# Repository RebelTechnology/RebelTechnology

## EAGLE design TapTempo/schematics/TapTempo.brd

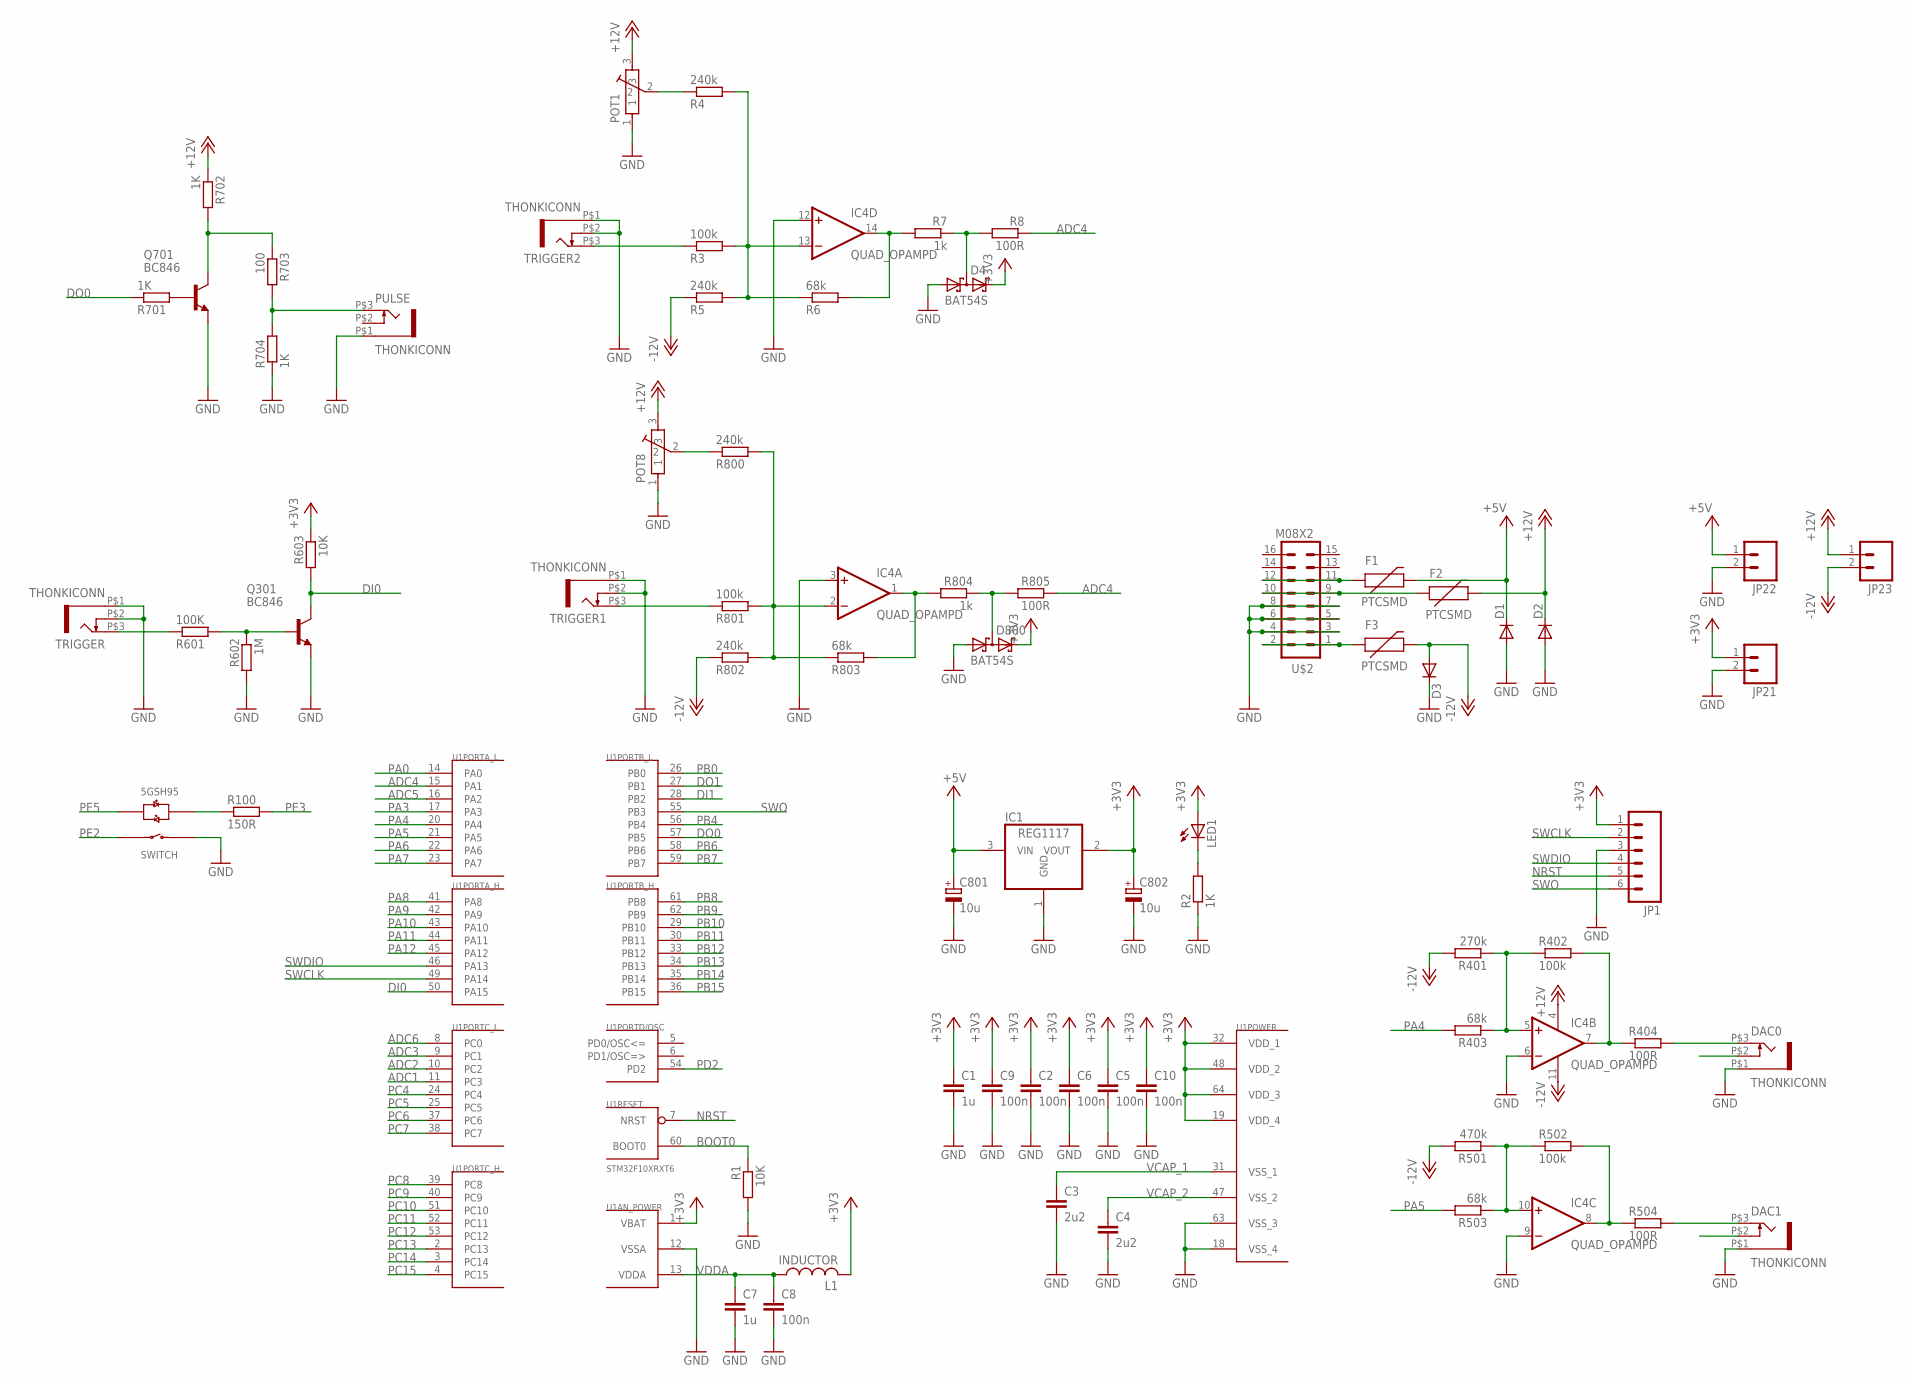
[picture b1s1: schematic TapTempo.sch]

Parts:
C1, C7: 1u; C0603
C2, C5, C6, C8, C9, C10: 100n; C0603
C3, C4: 2u2; C0603
C801, C802: 10u; PANASONIC_A
D1, D2, D3: DIODESMA; SMA-DIODE
D4, D800: BAT54S; SOT23
DAC0, DAC1: THONKICONN
F1, F2, F3: PTCSMD; PTC-1206
IC1: REG1117; SOT223
IC4: QUAD_OPAMPD; SO14
JP1: M06SIP; 1X06
JP21, JP22, JP23: M02PTH; 1X02
L1: INDUCTOR; 0603@1
LED1: LEDCHIPLED_0603; CHIPLED_0603
POT1, POT8: POT-ALPS-RK09L1140
PULSE: THONKICONN
Q301, Q701: BC846; SOT23
R1, R603: 10K; R0603
R2, R701, R702, R704: 1K; R0603
R3, R801: 100k; 0603
R4, R5, R800, R802: 240k; 0603
R6, R803: 68k; 0603
R7, R804: 1k; 0603
R8, R805: 100R; 0603
R100: 150R; 0603
R401: 270k; R0603
R402, R502: 100k; R0603
R403, R503: 68k; R0603
R404, R504: 100R; R0603
R501: 470k; R0603
R601: 100K; R0603
R602: 1M; R0603
R703: 100; R0603
TRIGGER, TRIGGER1, TRIGGER2: THONKICONN
U1: STM32F10XRXT6; TQFP64
U$1: 5GTH9
U$2: M08X2; 2X8

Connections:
+3V3: C1.1, C2.1, C5.1, C6.1, C9.1, C10.1, C802.+, D4.2 (C2), D800.2 (C2), IC1.2 (VOUT), JP1.1, JP21.1, L1.2, LED1.A, R603.1, U1.1 (VBAT), U1.19 (VDD_4), U1.32 (VDD_1), U1.48 (VDD_2), U1.64 (VDD_3)
+5V: C801.+, D1.C, F1.2, IC1.3 (VIN), JP22.1
+12V: D2.C, F2.2, IC4.4 (V+), JP23.1, POT1.3, POT8.3, R702.1
-12V: D3.A, F3.2, IC4.11 (V-), JP23.2, R5.1, R401.2, R501.2, R802.1
ADC1: U1.11 (PC3)
ADC2: U1.10 (PC2)
ADC3: U1.9 (PC1)
ADC4: R8.1, R805.1, U1.15 (PA1)
ADC5: U1.16 (PA2)
ADC6: U1.8 (PC0)
BOOT0: R1.1, U1.60 (BOOT0)
DI0: Q301.3 (C), R603.2, U1.50 (PA15)
DI1: U1.28 (PB2)
DO0: R701.1, U1.57 (PB5)
DO1: U1.27 (PB1)
GND: C1.2, C2.2, C3.2, C4.2, C5.2, C6.2, C7.2, C8.2, C9.2, C10.2, C801.-, C802.-, D1.A, D2.A, D3.C, D4.1 (A1), D800.1 (A1), DAC0.P$1 (5), DAC1.P$1 (5), IC1.1 (GND), IC4.3 (+IN), IC4.6 (-IN), IC4.9 (-IN), IC4.12 (+IN), JP1.3, JP21.2, JP22.2, POT1.1, POT8.1, PULSE.P$1 (5), Q301.2 (E), Q701.2 (E), R1.2, R2.1, R602.2, R704.1, TRIGGER.P$1 (5), TRIGGER.P$2 (4), TRIGGER1.P$1 (5), TRIGGER1.P$2 (4), TRIGGER2.P$1 (5), TRIGGER2.P$2 (4), U1.12 (VSSA), U1.18 (VSS_4), U1.63 (VSS_3), U$1.1 (SWITCH_B), U$2.3, U$2.4, U$2.5, U$2.6, U$2.7, U$2.8
unnamed: R801.1, TRIGGER1.P$3 (3)
unnamed: POT8.2, R800.1
unnamed: IC4.1 (OUT), R803.2, R804.2
unnamed: R3.1, TRIGGER2.P$3 (3)
unnamed: IC4.8 (OUT), R502.2, R504.1
unnamed: F3.1, U$2.1, U$2.2
unnamed: IC4.7 (OUT), R402.2, R404.1
unnamed: IC4.13 (-IN), R3.2, R4.2, R5.2, R6.1
unnamed: R100.1, U$1.+3 (LED_R+)
unnamed: POT1.2, R4.1
unnamed: IC4.14 (OUT), R6.2, R7.2
unnamed: IC4.5 (+IN), R401.1, R402.1, R403.1
unnamed: D4.3 (C1A2), R7.1, R8.2
unnamed: IC4.10 (+IN), R501.1, R502.1, R503.1
unnamed: LED1.C, R2.2
unnamed: R601.1, TRIGGER.P$3 (3)
unnamed: Q301.1 (B), R601.2, R602.1
unnamed: DAC0.P$3 (3), R404.2
unnamed: DAC1.P$3 (3), R504.2
unnamed: IC4.2 (-IN), R800.2, R801.2, R802.2, R803.1
unnamed: Q701.1 (B), R701.2
unnamed: PULSE.P$3 (3), R703.2, R704.2
unnamed: D800.3 (C1A2), R804.1, R805.2
unnamed: Q701.3 (C), R702.2, R703.1
unnamed: F1.1, U$2.11, U$2.12
unnamed: F2.1, U$2.9, U$2.10
NRST: JP1.5, U1.7 (NRST)
PA0: U1.14 (PA0)
PA3: U1.17 (PA3)
PA4: R403.2, U1.20 (PA4)
PA5: R503.2, U1.21 (PA5)
PA6: U1.22 (PA6)
PA7: U1.23 (PA7)
PA8: U1.41 (PA8)
PA9: U1.42 (PA9)
PA10: U1.43 (PA10)
PA11: U1.44 (PA11)
PA12: U1.45 (PA12)
PB0: U1.26 (PB0)
PB4: U1.56 (PB4)
PB6: U1.58 (PB6)
PB7: U1.59 (PB7)
PB8: U1.61 (PB8)
PB9: U1.62 (PB9)
PB10: U1.29 (PB10)
PB11: U1.30 (PB11)
PB12: U1.33 (PB12)
PB13: U1.34 (PB13)
PB14: U1.35 (PB14)
PB15: U1.36 (PB15)
PC4: U1.24 (PC4)
PC5: U1.25 (PC5)
PC6: U1.37 (PC6)
PC7: U1.38 (PC7)
PC8: U1.39 (PC8)
PC9: U1.40 (PC9)
PC10: U1.51 (PC10)
PC11: U1.52 (PC11)
PC12: U1.53 (PC12)
PC13: U1.2 (PC13)
PC14: U1.3 (PC14)
PC15: U1.4 (PC15)
PD2: U1.54 (PD2)
PE2: U$1.4 (SWITCH_A)
PE3: R100.2
PE5: U$1.-2 (LED_G+)
SWCLK: JP1.2, U1.49 (PA14)
SWDIO: JP1.4, U1.46 (PA13)
SWO: JP1.6, U1.55 (PB3)
VCAP_1: C3.1, U1.31 (VSS_1)
VCAP_2: C4.1, U1.47 (VSS_2)
VDDA: C7.1, C8.1, L1.1, U1.13 (VDDA)

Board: 2 copper layers, 72 parts (0 on the bottom side), 44 nets, no tracks yet.

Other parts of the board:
U$3: RT-LOGO-35MM-BL

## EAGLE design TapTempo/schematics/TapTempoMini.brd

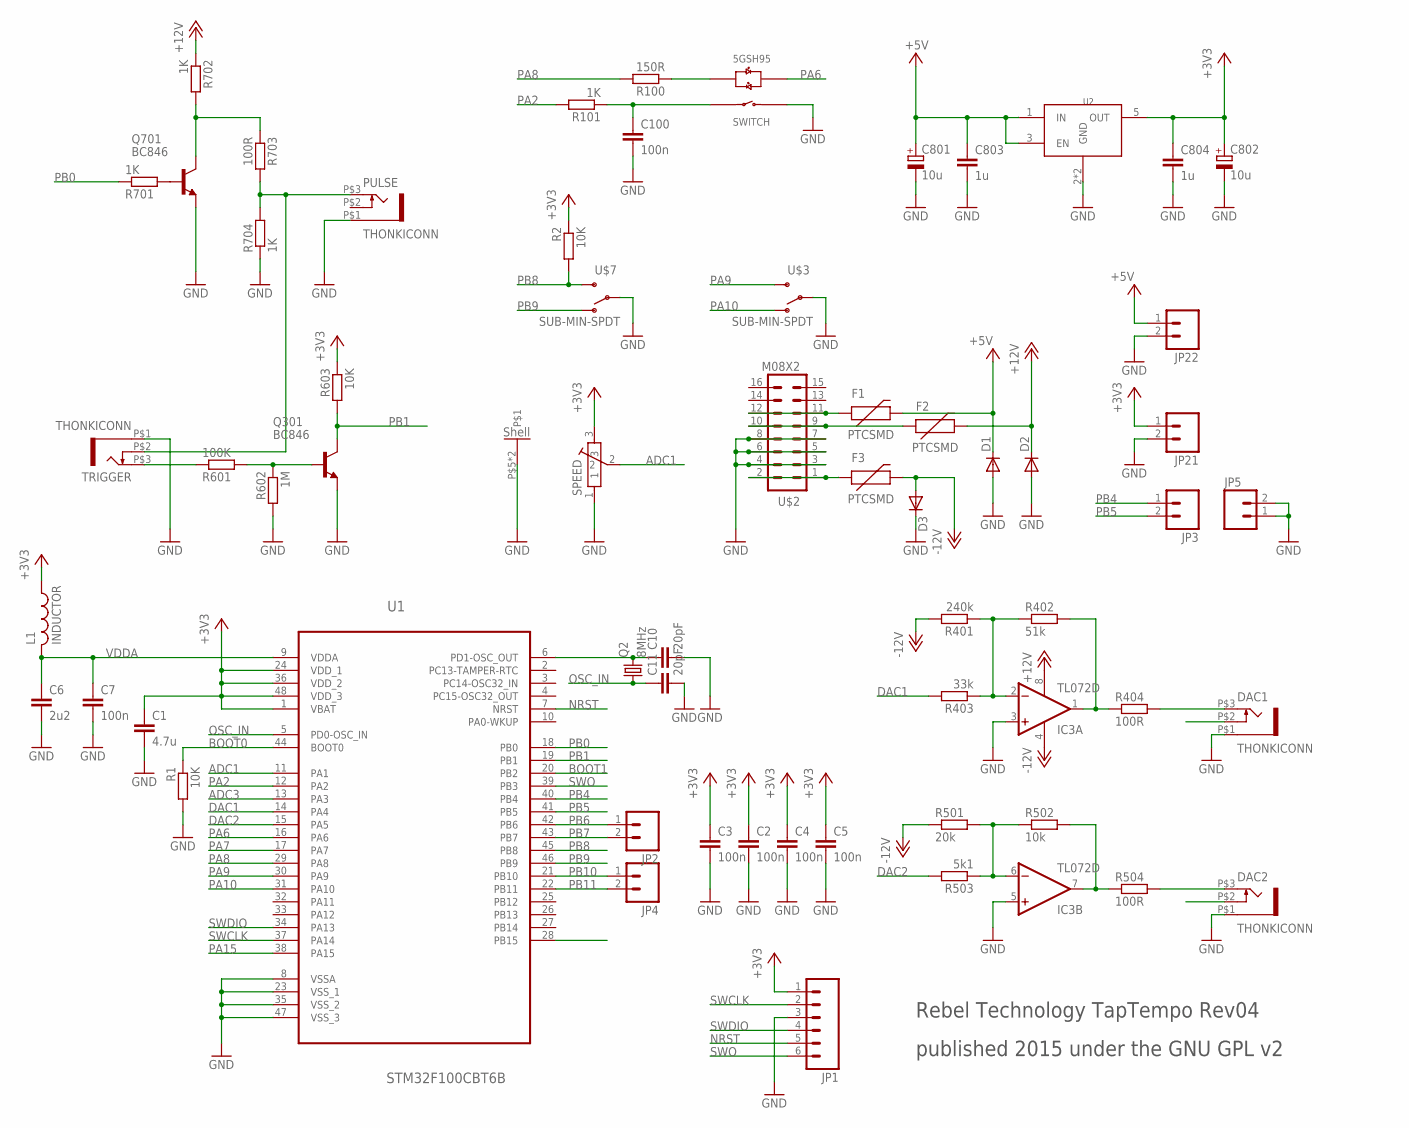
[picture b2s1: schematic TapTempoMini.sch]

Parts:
C1: 4.7u; C0603
C2, C3, C4, C5, C7, C100: 100n; C0603
C6: 2u2; C0603
C10, C11: 20pF; C0603
C801, C802: 10u; SANYO-OSCON_SMD_A5
C803, C804: 1u; C0603
D1, D2, D3: DIODESMA; SMA-DIODE
DAC1, DAC2: THONKICONN
F1, F2, F3: PTCSMD; PTC-1206
IC3: TL072D; SO08
JP1: M06SIP; 1X06
JP2, JP3, JP4, JP5, JP21, JP22: M02PTH; 1X02
L1: INDUCTOR; 0603
PULSE: THONKICONN
Q2: 8MHz; HC49UP; FARNELL 206-3972
Q301, Q701: BC846; SOT23
R1, R2, R603: 10K; R0603
R100: 150R; 0603
R101, R701, R702, R704: 1K; R0603
R401: 240k; R0603
R402: 51k; R0603
R403: 33k; R0603
R404, R504, R703: 100R; R0603
R501: 20k; R0603
R502: 10k; R0603
R503: 5k1; R0603
R601: 100K; R0603
R602: 1M; R0603
SPEED: POT-ALPS-RK09L1140
TRIGGER: THONKICONN
U1: STM32F100CBT6B; QFP50P900X900X160-48N
U2: NCP702; TSOP-5
U$1: 5GTH9
U$2: M08X2; 2X8
U$3, U$7: SUB-MIN-SPDT

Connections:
+3V3: C1.1, C2.1, C3.1, C4.1, C5.1, C802.+, C804.1, JP1.1, JP21.1, L1.1, R2.1, R603.1, SPEED.3, U1.1 (VBAT), U1.24 (VDD_1), U1.36 (VDD_2), U1.48 (VDD_3), U2.5 (OUT)
+5V: C801.+, C803.1, D1.C, F1.2, JP22.1, U2.1 (IN), U2.3 (EN)
+12V: D2.C, F2.2, IC3.8 (V+), R702.1
-12V: D3.A, F3.2, IC3.4 (V-), R401.2, R501.1
ADC1: SPEED.2, U1.11 (PA1)
ADC3: U1.13 (PA3)
BOOT0: R1.1, U1.44 (BOOT0)
BOOT1: U1.20 (PB2)
DAC1: R403.2, U1.14 (PA4)
DAC2: R503.2, U1.15 (PA5)
GND: C1.2, C2.2, C3.2, C4.2, C5.2, C6.2, C7.2, C10.2, C11.2, C100.2, C801.-, C802.-, C803.2, C804.2, D1.A, D2.A, D3.C, DAC1.P$1 (5), DAC2.P$1 (5), IC3.3 (+IN), IC3.5 (+IN), JP1.3, JP5.1, JP5.2, JP21.2, JP22.2, PULSE.P$1 (5), Q301.2 (E), Q701.2 (E), R1.2, R602.2, R704.1, SPEED.1, SPEED.P$5, SPEED.P$6, TRIGGER.P$1 (5), U1.8 (VSSA), U1.23 (VSS_1), U1.35 (VSS_2), U1.47 (VSS_3), U2.2 (GND), U2.4 (GND), U$1.1 (SWITCH_B), U$2.3, U$2.4, U$2.5, U$2.6, U$2.7, U$2.8, U$3.2, U$7.2
unnamed: C10.1, Q2.2, U1.6 (PD1-OSC_OUT)
unnamed: R100.1, U$1.-2 (LED_G+)
unnamed: IC3.7 (OUT), R502.2, R504.1
unnamed: IC3.6 (-IN), R501.2, R502.1, R503.1
unnamed: PULSE.P$3 (3), R703.2, R704.2, TRIGGER.P$2 (4)
unnamed: F3.1, U$2.1, U$2.2
unnamed: IC3.1 (OUT), R402.2, R404.1
unnamed: IC3.2 (-IN), R401.1, R402.1, R403.1
unnamed: R601.1, TRIGGER.P$3 (3)
unnamed: Q301.1 (B), R601.2, R602.1
unnamed: DAC1.P$3 (3), R404.2
unnamed: DAC2.P$3 (3), R504.2
unnamed: Q701.1 (B), R701.2
unnamed: Q701.3 (C), R702.2, R703.1
unnamed: F1.1, U$2.11, U$2.12
unnamed: F2.1, U$2.9, U$2.10
NRST: JP1.5, U1.7 (NRST)
OSC_IN: C11.1, Q2.1, U1.5 (PD0-OSC_IN)
PA2: R101.2, U1.12 (PA2)
PA6: U1.16 (PA6), U$1.+3 (LED_R+)
PA7: U1.17 (PA7)
PA8: R100.2, U1.29 (PA8)
PA9: U1.30 (PA9), U$3.3 (S)
PA10: U1.31 (PA10), U$3.1 (O)
PA15: U1.38 (PA15)
PB0: R701.1, U1.18 (PB0)
PB1: Q301.3 (C), R603.2, U1.19 (PB1)
PB4: JP3.1, U1.40 (PB4)
PB5: JP3.2, U1.41 (PB5)
PB6: JP2.1, U1.42 (PB6)
PB7: JP2.2, U1.43 (PB7)
PB8: R2.2, U1.45 (PB8), U$7.3 (S)
PB9: U1.46 (PB9), U$7.1 (O)
PB10: JP4.1, U1.21 (PB10)
PB11: JP4.2, U1.22 (PB11)
SWCLK: JP1.2, U1.37 (PA14)
SWDIO: JP1.4, U1.34 (PA13)
SWITCH_A: C100.1, R101.1, U$1.4 (SWITCH_A)
SWO: JP1.6, U1.39 (PB3)
VDDA: C6.1, C7.1, L1.2, U1.9 (VDDA)

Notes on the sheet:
Rebel Technology TapTempo Rev04
published 2015 under the GNU GPL v2

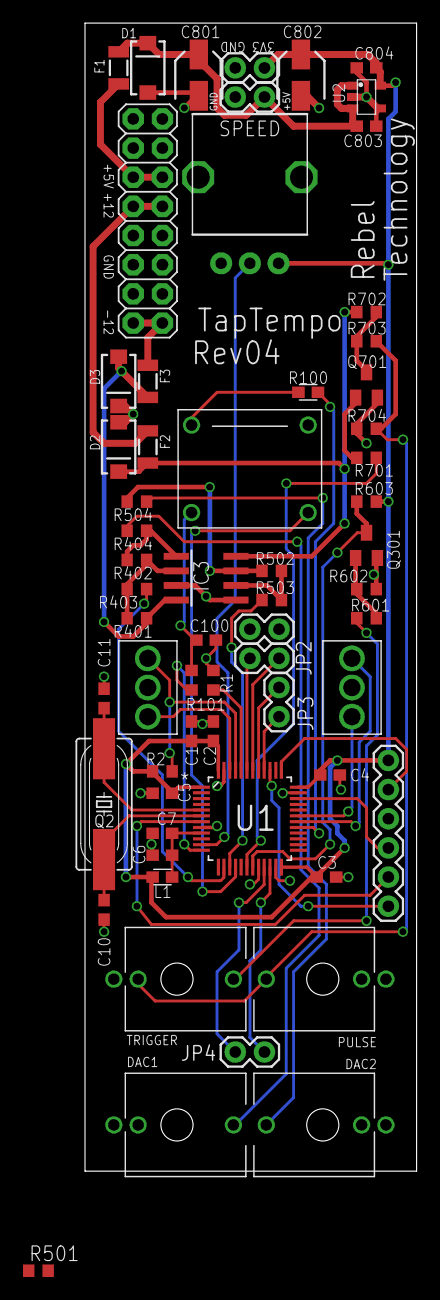
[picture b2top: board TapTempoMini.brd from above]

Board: 2 copper layers, 28.9 x 100.0 mm, 62 parts (0 on the bottom side), 47 nets.

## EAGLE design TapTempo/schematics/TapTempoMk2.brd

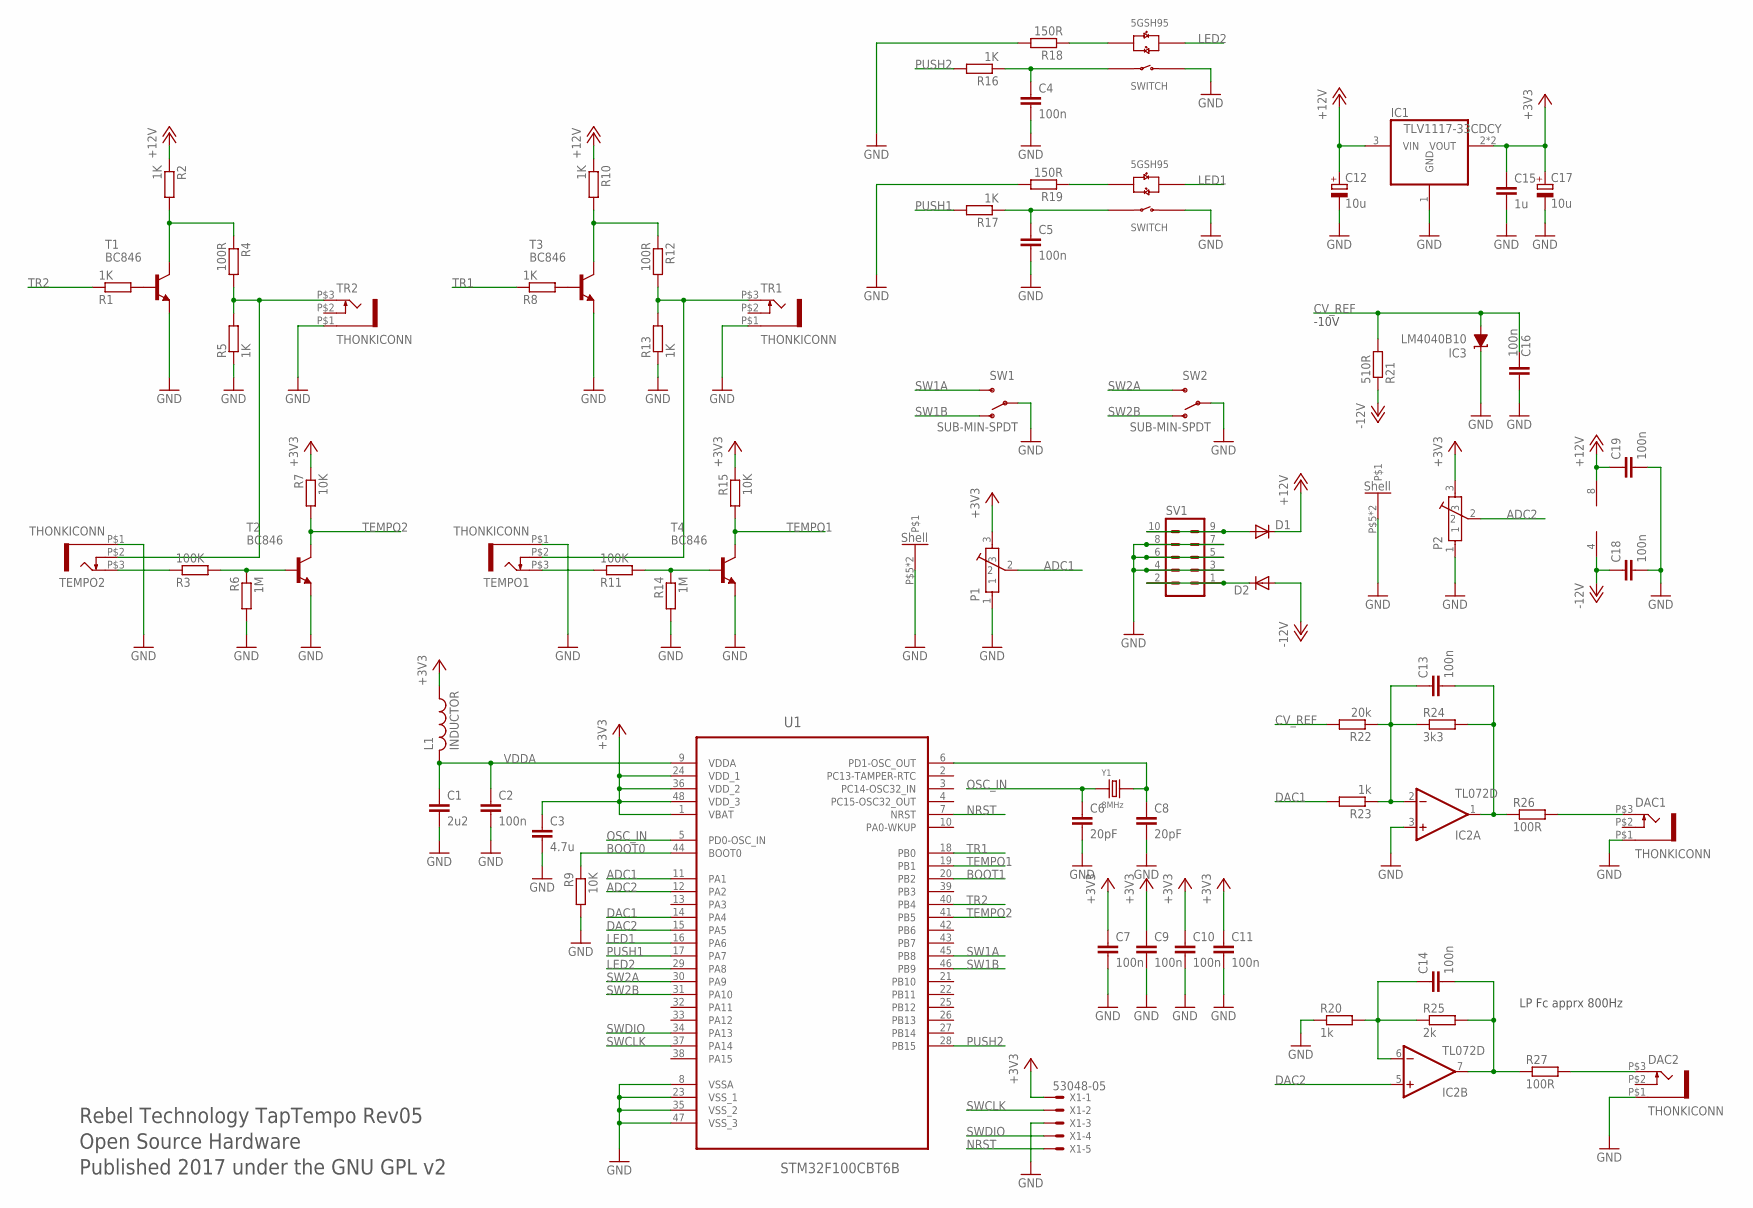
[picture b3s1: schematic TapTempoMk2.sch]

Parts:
C1: 2u2; C0603
C2, C4, C5, C7, C9, C10, C11, C13, C14, C16, C18, C19: 100n; C0603
C3: 4.7u; C0603
C6, C8: 20pF; C0603
C12, C17: 10u; PANASONIC_A; FARNELL 882-3014
C15: 1u; C0603
D1, D2: DIODESMA; SMA-DIODE
DAC1, DAC2: THONKICONN
IC1: TLV1117-33CDCY; SOT223; FARNELL 149-4942
IC2: TL072D; SO08
IC3: LM4040B10; DBZ_R-PDSO-G3
L1: INDUCTOR; 0603
P1, P2: POT-ALPS-RK09L1140
PUSH1, PUSH2: 5GTH9
R1, R2, R5, R8, R10, R13, R16, R17: 1K; 0603
R3, R11: 100K; 0603
R4, R12, R26, R27: 100R; 0603
R6, R14: 1M; 0603
R7, R9, R15: 10K; 0603
R18, R19: 150R; 0603
R20, R23: 1k; 0603
R21: 510R; 0603
R22: 20k; 0603
R24: 3k3; 0603
R25: 2k; 0603
SV1: MA05-2
SW1, SW2: SUB-MIN-SPDT
T1, T2, T3, T4: BC846; SOT23
TEMPO1, TEMPO2: THONKICONN
TR1, TR2: THONKICONN
U1: STM32F100CBT6B; QFP50P900X900X160-48N
X1: 53048-05
Y1: 8MHz; X2-SMD-5.0X3.2X1.3MM

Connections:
+3V3: C3.1, C7.1, C9.1, C10.1, C11.1, C15.1, C17.+, IC1.2 (VOUT), IC1.4 (VOUT), L1.1, P1.3, P2.3, R7.1, R15.1, U1.1 (VBAT), U1.24 (VDD_1), U1.36 (VDD_2), U1.48 (VDD_3), X1.1
+12V: C12.+, C19.1, D1.C, IC1.3 (VIN), IC2.8 (V+), R2.1, R10.1
-12V: C18.1, D2.A, IC2.4 (V-), R21.1
ADC1: P1.2, U1.11 (PA1)
ADC2: P2.2, U1.12 (PA2)
BOOT0: R9.1, U1.44 (BOOT0)
BOOT1: U1.20 (PB2)
CV_REF: C16.1, IC3.2 (A), R21.2, R22.2
DAC1: R23.2, U1.14 (PA4)
DAC2: IC2.5 (+IN), U1.15 (PA5)
GND: C1.2, C2.2, C3.2, C4.2, C5.2, C6.2, C7.2, C8.2, C9.2, C10.2, C11.2, C12.-, C15.2, C16.2, C17.-, C18.2, C19.2, DAC1.P$1 (5), DAC2.P$1 (5), IC1.1 (GND), IC2.3 (+IN), IC3.1 (C), P1.1, P1.P$5, P1.P$6, P2.1, P2.P$5, P2.P$6, PUSH1.1 (SWITCH_B), PUSH2.1 (SWITCH_B), R5.1, R6.2, R9.2, R13.1, R14.2, R18.2, R19.2, R20.1, SV1.3, SV1.4, SV1.5, SV1.6, SV1.7, SV1.8, SW1.2, SW2.2, T1.2 (E), T2.2 (E), T3.2 (E), T4.2 (E), TEMPO1.P$1 (5), TEMPO2.P$1 (5), TR1.P$1 (5), TR2.P$1 (5), U1.8 (VSSA), U1.23 (VSS_1), U1.35 (VSS_2), U1.47 (VSS_3), X1.3
LED1: PUSH1.+3 (LED_R+), U1.16 (PA6)
LED2: PUSH2.+3 (LED_R+), U1.29 (PA8)
unnamed: C8.1, U1.6 (PD1-OSC_OUT), Y1.2
unnamed: PUSH1.-2 (LED_G+), R19.1
unnamed: C14.2, IC2.7 (OUT), R25.2, R27.1
unnamed: C14.1, IC2.6 (-IN), R20.2, R25.1
unnamed: R12.2, R13.2, TEMPO1.P$2 (4), TR1.P$3 (3)
unnamed: D1.A, SV1.9, SV1.10
unnamed: C13.2, IC2.1 (OUT), R24.2, R26.1
unnamed: PUSH2.-2 (LED_G+), R18.1
unnamed: R3.2, R6.1, T2.1 (B)
unnamed: R1.2, T1.1 (B)
unnamed: R2.2, R4.1, T1.3 (C)
unnamed: C13.1, IC2.2 (-IN), R22.1, R23.1, R24.1
unnamed: R3.1, TEMPO2.P$3 (3)
unnamed: R4.2, R5.2, TEMPO2.P$2 (4), TR2.P$3 (3)
unnamed: D2.C, SV1.1, SV1.2
unnamed: C5.1, PUSH1.4 (SWITCH_A), R17.1
unnamed: C4.1, PUSH2.4 (SWITCH_A), R16.1
unnamed: R11.1, TEMPO1.P$3 (3)
unnamed: R11.2, R14.1, T4.1 (B)
unnamed: DAC1.P$3 (3), R26.2
unnamed: DAC2.P$3 (3), R27.2
unnamed: R8.2, T3.1 (B)
unnamed: R10.2, R12.1, T3.3 (C)
NRST: U1.7 (NRST), X1.5
OSC_IN: C6.1, U1.5 (PD0-OSC_IN), Y1.1
PUSH1: R17.2, U1.17 (PA7)
PUSH2: R16.2, U1.28 (PB15)
SW1A: SW1.3 (S), U1.45 (PB8)
SW1B: SW1.1 (O), U1.46 (PB9)
SW2A: SW2.3 (S), U1.30 (PA9)
SW2B: SW2.1 (O), U1.31 (PA10)
SWCLK: U1.37 (PA14), X1.2
SWDIO: U1.34 (PA13), X1.4
TEMPO1: R15.2, T4.3 (C), U1.19 (PB1)
TEMPO2: R7.2, T2.3 (C), U1.41 (PB5)
TR1: R8.1, U1.18 (PB0)
TR2: R1.1, U1.40 (PB4)
VDDA: C1.1, C2.1, L1.2, U1.9 (VDDA)

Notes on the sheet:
Rebel Technology TapTempo Rev05
Published 2017 under the GNU GPL v2
LP Fc apprx 800Hz
-10V
Open Source Hardware

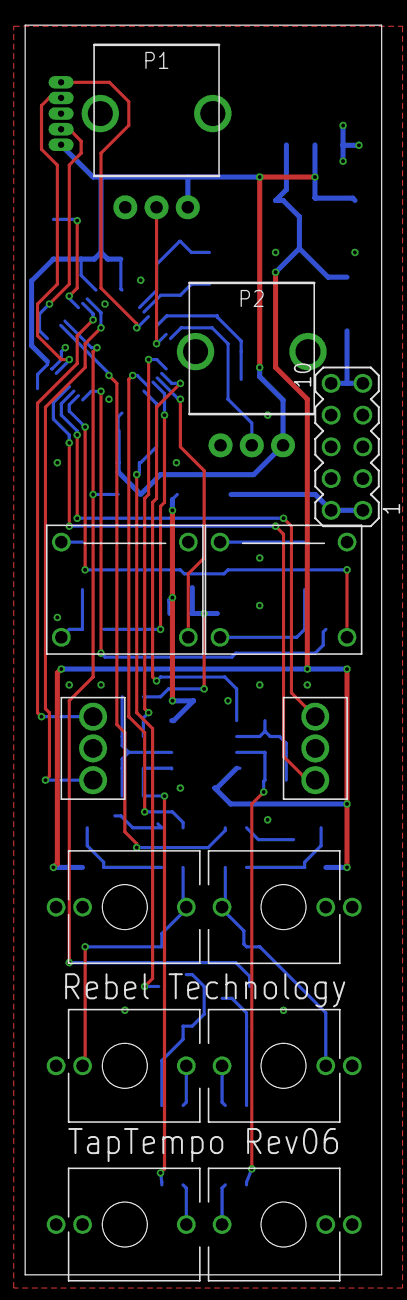
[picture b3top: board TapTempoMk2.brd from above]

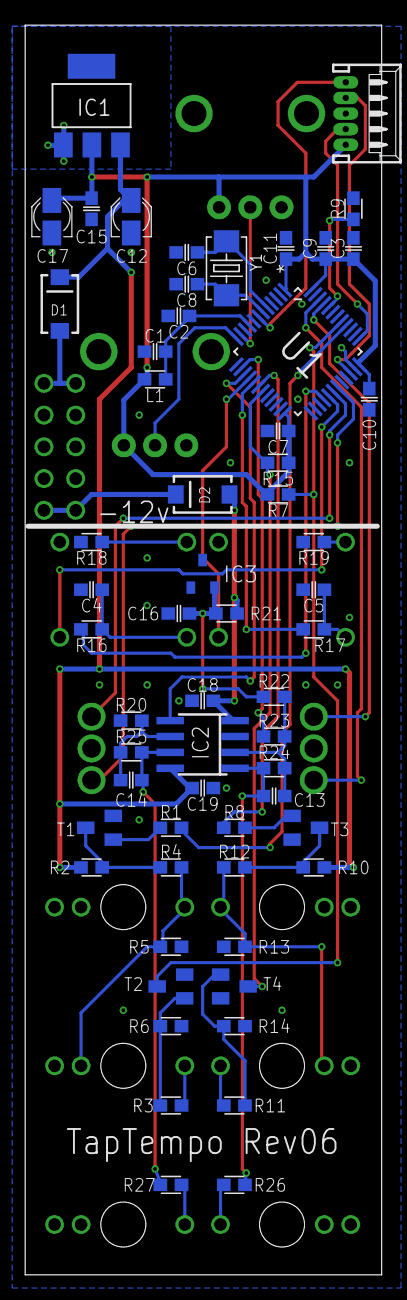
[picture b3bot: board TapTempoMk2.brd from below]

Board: 2 copper layers, 28.5 x 100.0 mm, 72 parts (59 on the bottom side), 50 nets.

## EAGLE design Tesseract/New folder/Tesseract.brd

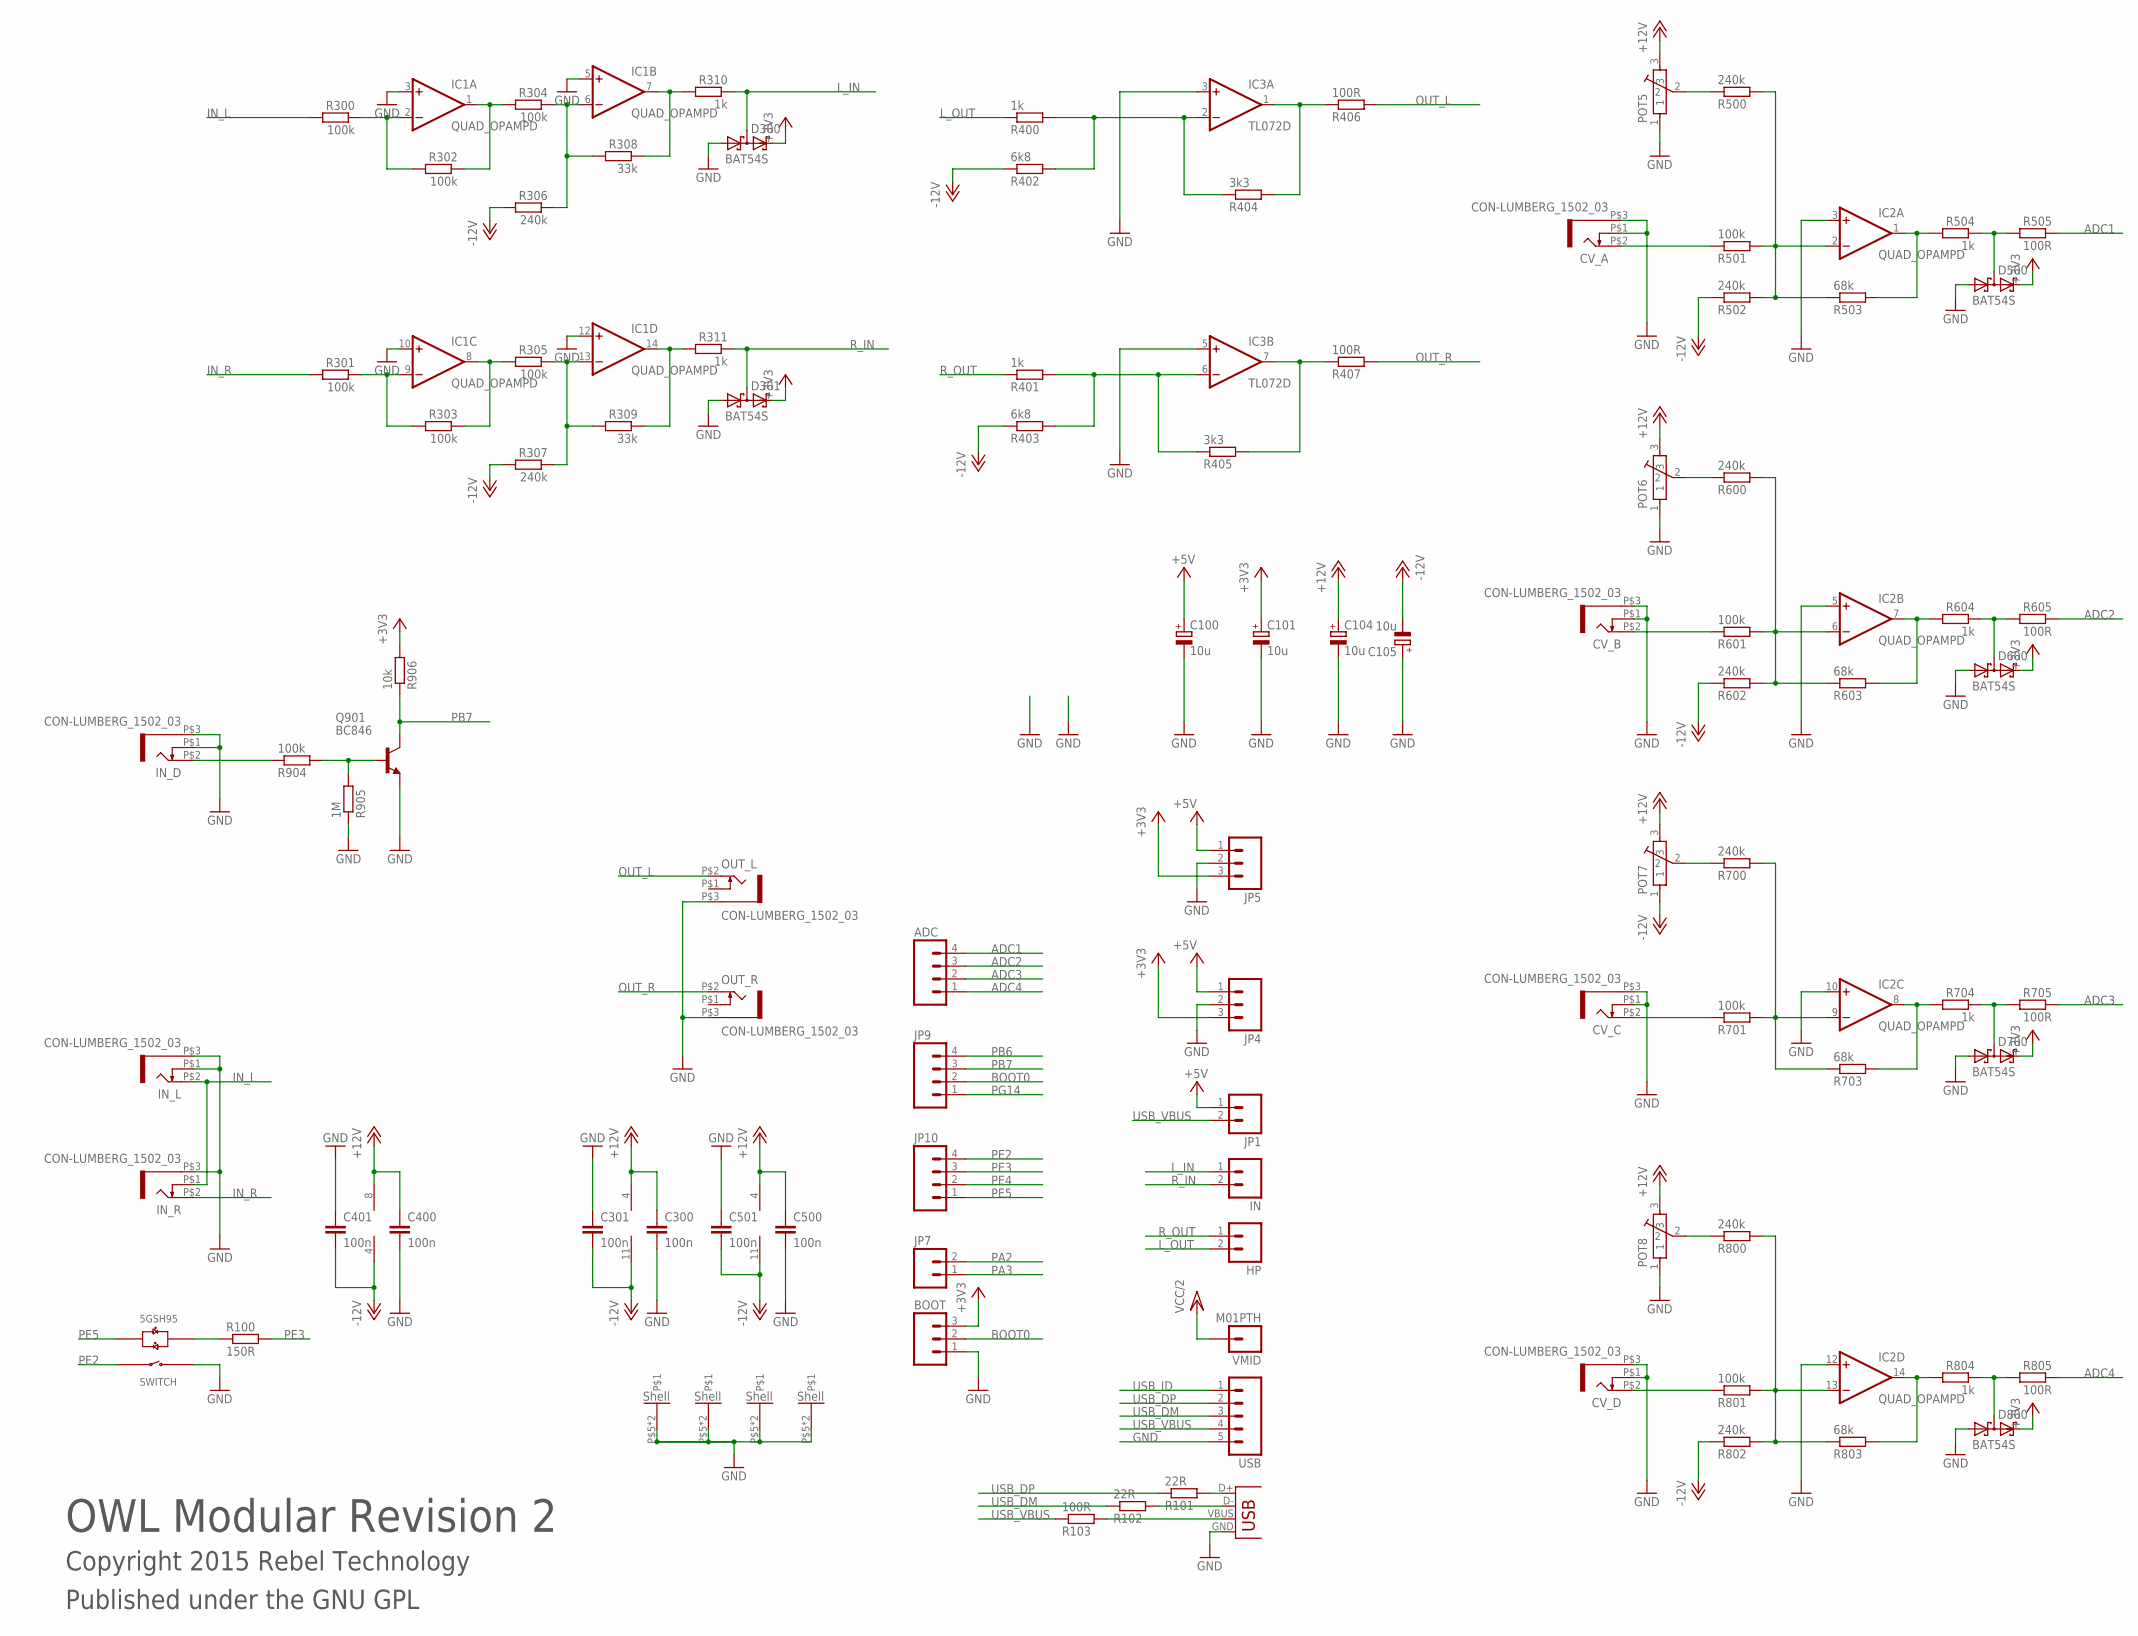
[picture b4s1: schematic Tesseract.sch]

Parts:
ADC: M04PTH; 1X04
BOOT: M03PTH; 1X03
C100, C101, C104, C105: 10u; PANASONIC_A
C300, C301, C400, C401, C500, C501: 100n; C0603
CV_A: CON-LUMBERG_1502_03
CV_B: CON-LUMBERG_1502_03
CV_C: CON-LUMBERG_1502_03
CV_D: CON-LUMBERG_1502_03
D300, D301, D500, D600, D700, D800: BAT54S; SOT23
HP: M02PTH; 1X02
IC1, IC2: QUAD_OPAMPD; SO14
IC3: TL072D; SO08
IN: M02PTH; 1X02
IN_D: CON-LUMBERG_1502_03
IN_L: CON-LUMBERG_1502_03
IN_R: CON-LUMBERG_1502_03
JP1, JP7: M02PTH; 1X02
JP4, JP5: M03PTH; 1X03
JP9, JP10: M04PTH; 1X04
OUT_L: CON-LUMBERG_1502_03
OUT_R: CON-LUMBERG_1502_03
POT5, POT6, POT7, POT8: POT-ALPS-RK09L1140
Q901: BC846; SOT23
R100: 150R; 0603
R101, R102: 22R; 0603
R103, R406, R407, R505, R605, R705, R805: 100R; 0603
R300, R301, R302, R303, R304, R305, R501, R601, R701, R801, R904: 100k; 0603
R306, R307, R500, R502, R600, R602, R700, R800, R802: 240k; 0603
R308, R309: 33k; 0603
R310, R311, R400, R401, R504, R604, R704, R804: 1k; 0603
R402, R403: 6k8; 0603
R404, R405: 3k3; 0603
R503, R603, R703, R803: 68k; 0603
R905: 1M; 0603
R906: 10k; 0603
U$1: 5GTH9
USB: M05PTH; 1X05
VMID: M01PTH; 1X01
X1: USBPTH-VERTICAL; USB-B-PTH-VERTICAL

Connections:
+3V3: BOOT.3, C101.+, D300.2 (C2), D301.2 (C2), D500.2 (C2), D600.2 (C2), D700.2 (C2), D800.2 (C2), JP4.3, JP5.3, R906.2
+5V: C100.+, JP1.1, JP4.1, JP5.1
+12V: C104.+, C300.1, C400.1, C500.1, IC1.4 (V+), IC2.4 (V+), IC3.8 (V+), POT5.3, POT6.3, POT7.3, POT8.3
-12V: C105.-, C301.2, C401.2, C501.2, IC1.11 (V-), IC2.11 (V-), IC3.4 (V-), R306.2, R307.2, R402.1, R403.1, R502.1, R602.1, R802.1
ADC1: ADC.4, R505.1
ADC2: ADC.3, R605.1
ADC3: ADC.2, R705.1
ADC4: ADC.1, R805.1
BOOT0: BOOT.2, JP9.2
GND: BOOT.1, C100.-, C101.-, C104.-, C105.+, C300.2, C301.1, C400.2, C401.1, C500.2, C501.1, CV_A.P$1 (4), CV_A.P$3 (5), CV_B.P$1 (4), CV_B.P$3 (5), CV_C.P$1 (4), CV_C.P$3 (5), CV_D.P$1 (4), CV_D.P$3 (5), D300.1 (A1), D301.1 (A1), D500.1 (A1), D600.1 (A1), D700.1 (A1), D800.1 (A1), IC1.3 (+IN), IC1.5 (+IN), IC1.10 (+IN), IC1.12 (+IN), IC2.3 (+IN), IC2.5 (+IN), IC2.10 (+IN), IC2.12 (+IN), IC3.3 (+IN), IC3.5 (+IN), IN_D.P$1 (4), IN_D.P$3 (5), IN_L.P$1 (4), IN_L.P$3 (5), IN_R.P$3 (5), JP4.2, JP5.2, OUT_L.P$3 (5), OUT_R.P$3 (5), POT5.1, POT5.P$5, POT5.P$6, POT6.1, POT6.P$5, POT6.P$6, POT7.P$5, POT7.P$6, POT8.1, POT8.P$5, POT8.P$6, Q901.2 (E), R905.1, U$1.1 (SWITCH_B), USB.5, X1.GND
IN_L: IN_L.P$2 (3), IN_R.P$1 (4), R300.2
IN_R: IN_R.P$2 (3), R301.2
L_IN: D300.3 (C1A2), IN.1, R310.1
L_OUT: HP.2, R400.1
unnamed: IC1.1 (OUT), R302.1, R304.2
unnamed: CV_A.P$2 (3), R501.1
unnamed: IC1.8 (OUT), R303.1, R305.2
unnamed: IC1.9 (-IN), R301.1, R303.2
unnamed: IC1.13 (-IN), R305.1, R307.1, R309.2
unnamed: IC1.2 (-IN), R300.1, R302.2
unnamed: R100.1, U$1.+3 (LED_R+)
unnamed: IC2.2 (-IN), R500.2, R501.2, R502.2, R503.1
unnamed: POT5.2, R500.1
unnamed: D500.3 (C1A2), R504.1, R505.2
unnamed: IC2.1 (OUT), R503.2, R504.2
unnamed: CV_B.P$2 (3), R601.1
unnamed: IC2.6 (-IN), R600.2, R601.2, R602.2, R603.1
unnamed: POT6.2, R600.1
unnamed: IC2.7 (OUT), R603.2, R604.2
unnamed: D600.3 (C1A2), R604.1, R605.2
unnamed: CV_C.P$2 (3), R701.1
unnamed: IC2.9 (-IN), R700.2, R701.2, R703.1
unnamed: POT7.2, R700.1
unnamed: IC2.8 (OUT), R703.2, R704.2
unnamed: D700.3 (C1A2), R704.1, R705.2
unnamed: CV_D.P$2 (3), R801.1
unnamed: IC1.6 (-IN), R304.1, R306.1, R308.2
unnamed: IC2.13 (-IN), R800.2, R801.2, R802.2, R803.1
unnamed: POT8.2, R800.1
unnamed: IC2.14 (OUT), R803.2, R804.2
unnamed: D800.3 (C1A2), R804.1, R805.2
unnamed: Q901.1 (B), R904.2, R905.2
unnamed: IC3.1 (OUT), R404.2, R406.1
unnamed: IC3.7 (OUT), R405.2, R407.1
unnamed: IC3.2 (-IN), R400.2, R402.2, R404.1
unnamed: IC3.6 (-IN), R401.2, R403.2, R405.1
unnamed: IN_D.P$2 (3), R904.1
unnamed: R101.2, X1.D+
unnamed: R102.2, X1.D-
unnamed: IC1.14 (OUT), R309.1, R311.2
unnamed: R103.2, X1.VBUS
unnamed: IC1.7 (OUT), R308.1, R310.2
OUT_L: OUT_L.P$2 (3), R406.2
OUT_R: OUT_R.P$2 (3), R407.2
PA2: JP7.2
PA3: JP7.1
PB6: JP9.4
PB7: JP9.3, Q901.3 (C), R906.1
PE2: JP10.4, U$1.4 (SWITCH_A)
PE3: JP10.3, R100.2
PE4: JP10.2
PE5: JP10.1, U$1.-2 (LED_G+)
PG14: JP9.1
R_IN: D301.3 (C1A2), IN.2, R311.1
R_OUT: HP.1, R401.1
USB_DM: R102.1, USB.3
USB_DP: R101.1, USB.2
USB_ID: USB.1
USB_VBUS: JP1.2, R103.1, USB.4
VCC/2: VMID.1

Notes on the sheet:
OWL Modular Revision 2
Copyright 2015 Rebel Technology
Published under the GNU GPL

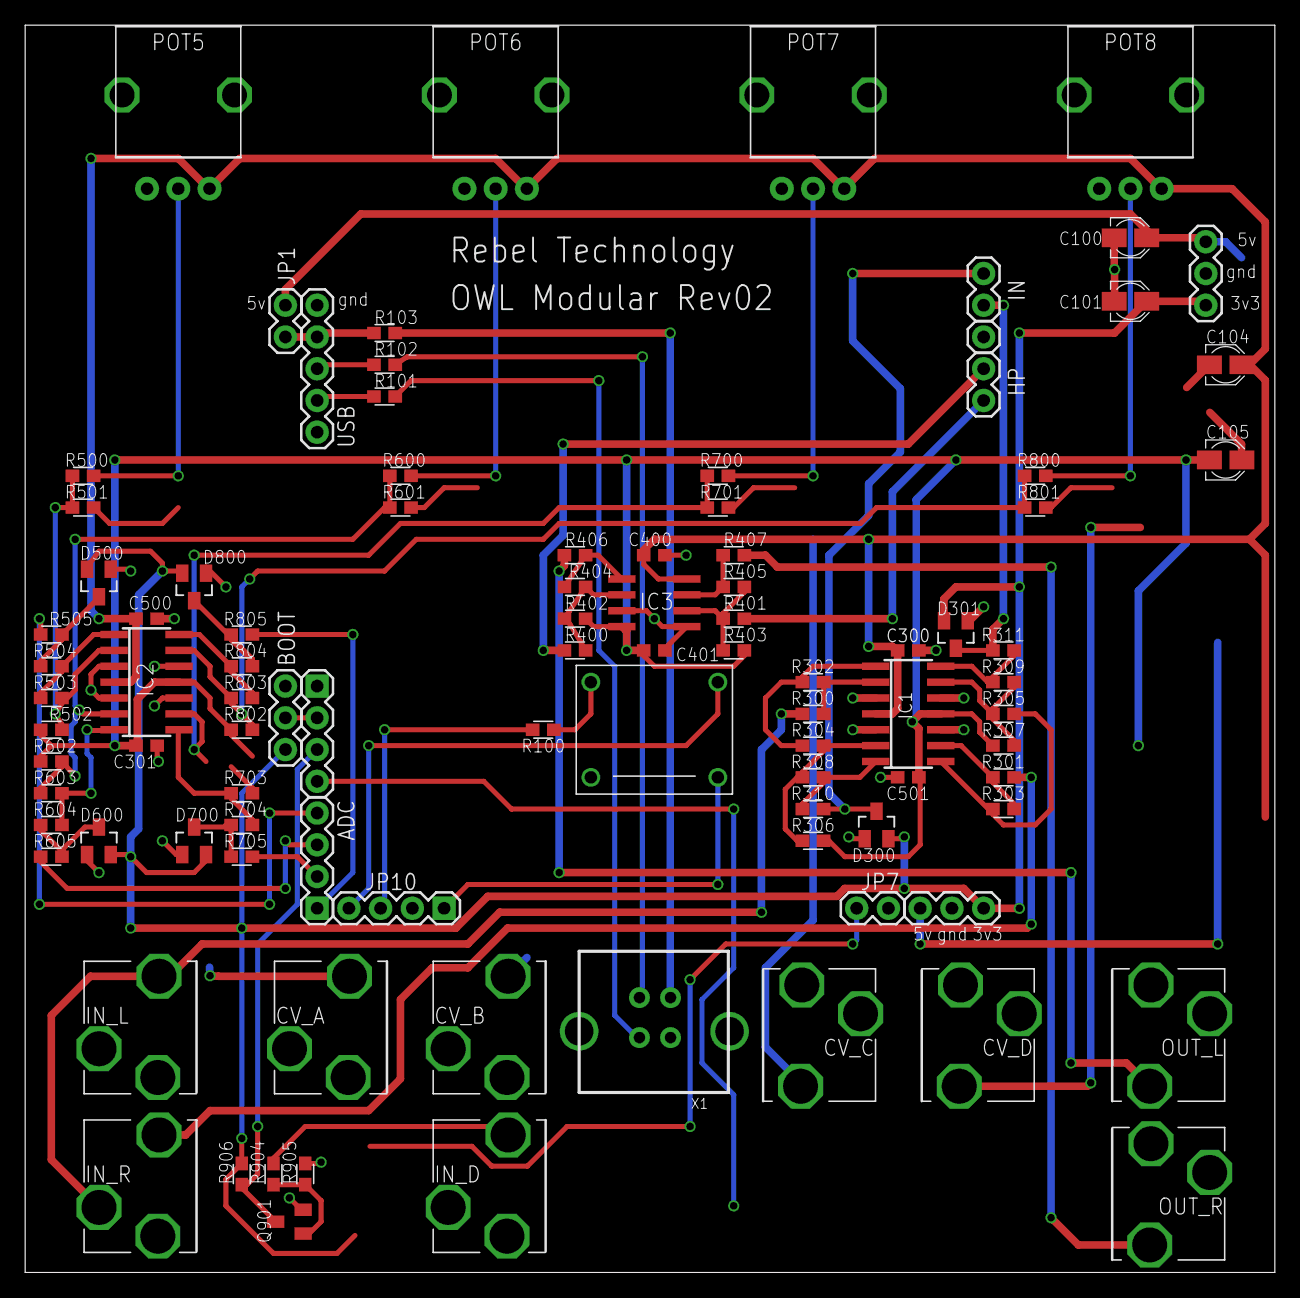
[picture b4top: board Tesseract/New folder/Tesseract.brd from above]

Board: 2 copper layers, 100.0 x 99.8 mm, 97 parts (0 on the bottom side), 63 nets.

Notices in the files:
parts and their libraries:
SparkFun: Licensing: CC v3.0 Share-Alike You are welcome to use this library for commercial purposes.
